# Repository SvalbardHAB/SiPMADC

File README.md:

# Existing SiPM ADC board

This board contains two dual-channel 10 bit 65MSPS MAX1182 ADCs; kindly provided by Maxim as free samples. There is also a MachXO2
CPLD for data processing, interfacing over SPI with a microcontroller. It is designed to obtain more  quantitative 
data from the SiPM and scintillator detector than the previous comparator board; at the expense of only using four of the 16 channels.

The board also contains the SiPM bias supply, consisting of a -34V inverting buck-boost converter and an op-amp to output the exact
voltage. This, along with the midpoint voltage - note this is not how the board is designed; during assembly a wire connecting 
Vmid to one of the DAC channels was added and U1 was not populated - is set by a TI DAC7564 allowing precise closed-case software adjustment.

At present the board has been assembled and tested. Unfortunately one of the ADC channels is not functioning correctly and
needs to be investigated further; this is suspected to be an assembly issue.

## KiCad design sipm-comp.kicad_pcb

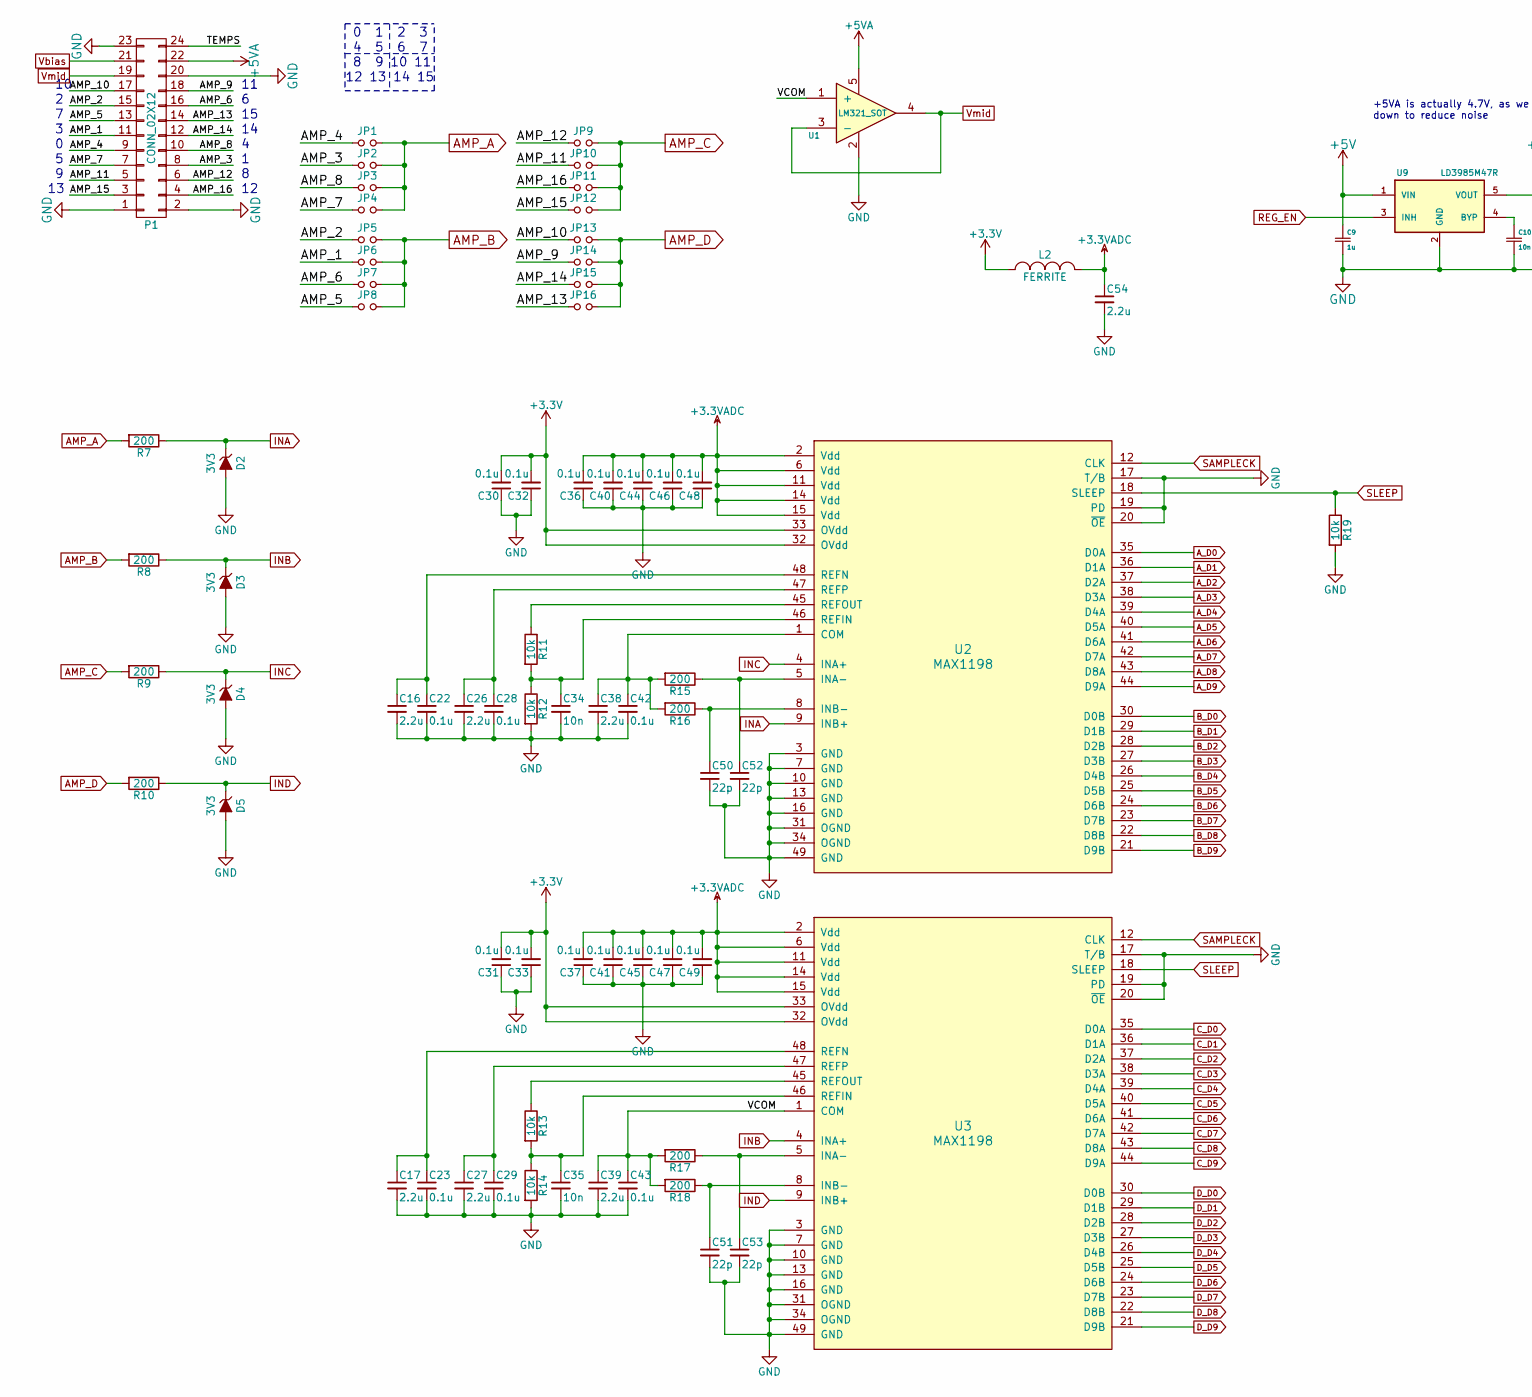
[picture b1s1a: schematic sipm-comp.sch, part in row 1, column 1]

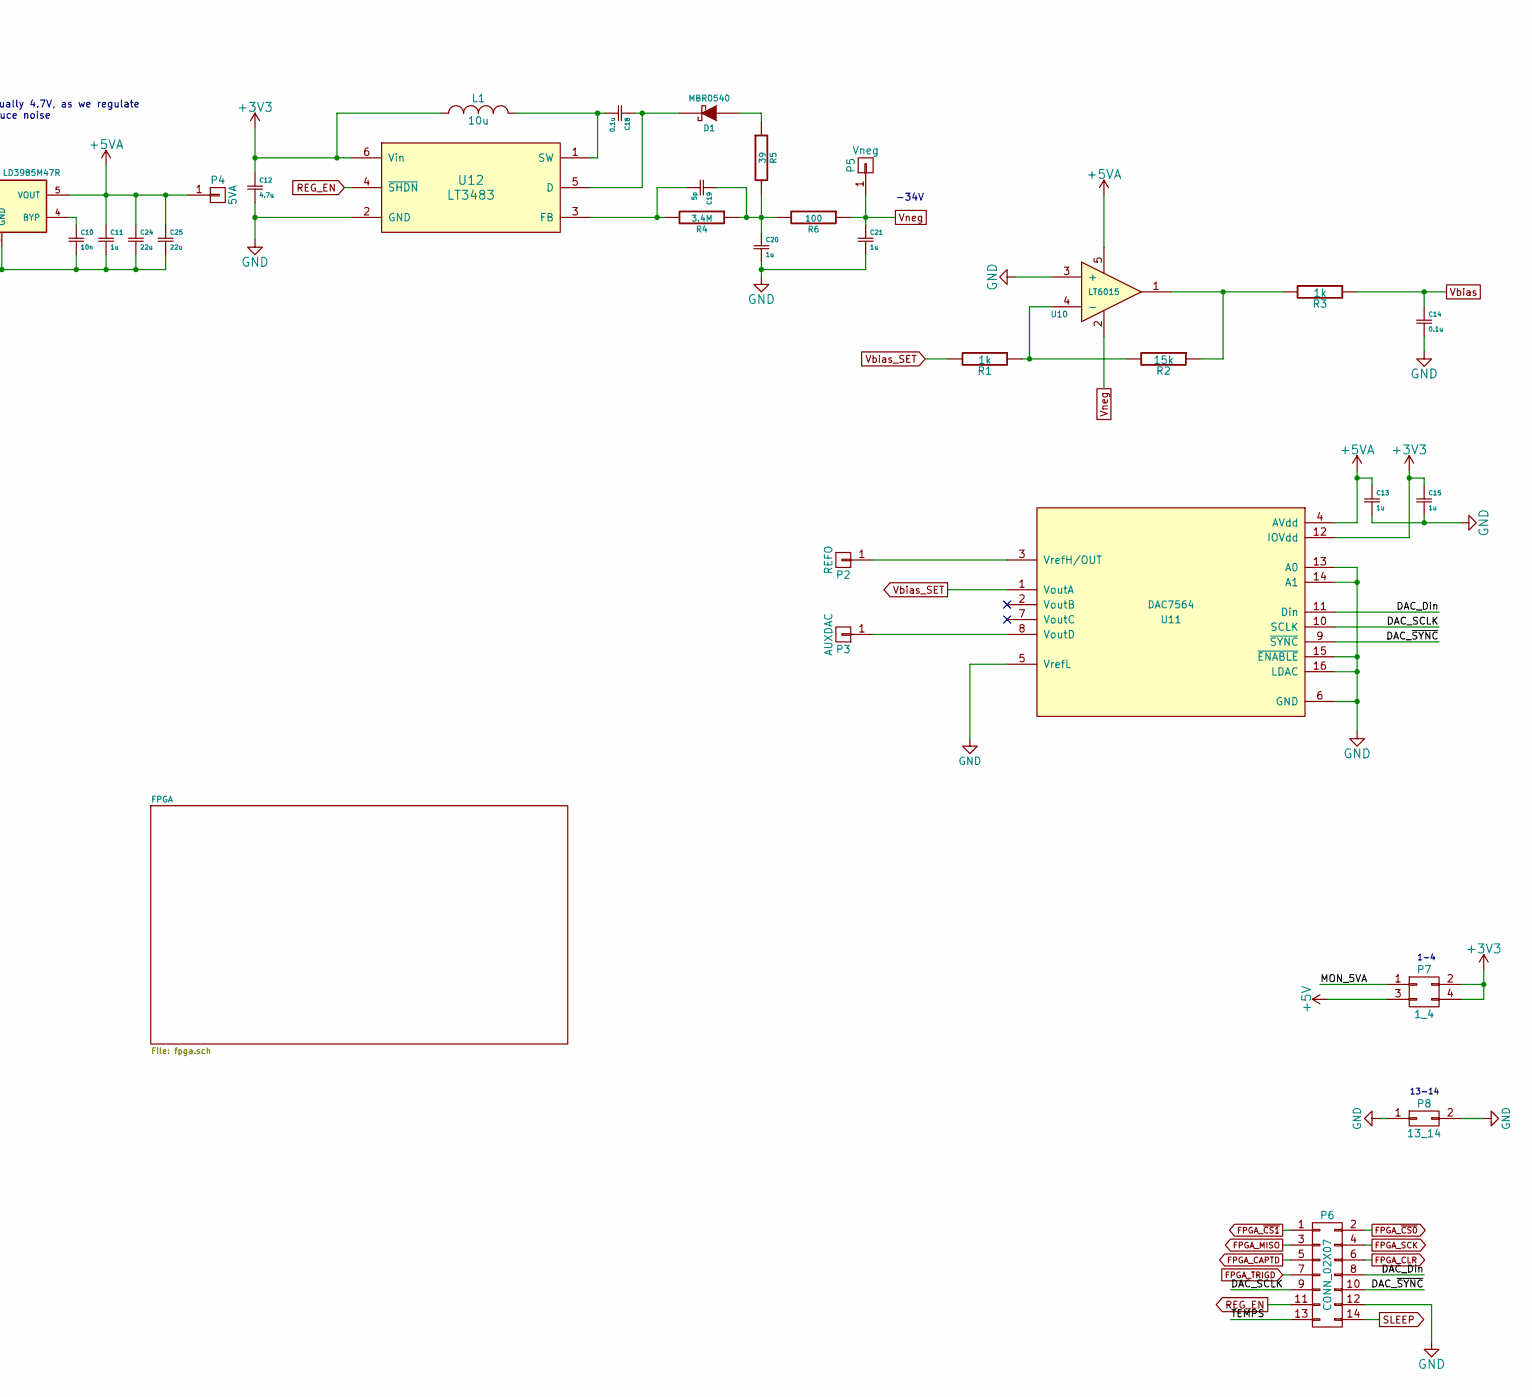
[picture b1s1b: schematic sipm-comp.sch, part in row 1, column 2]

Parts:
C9, C11, C13, C15: 1u; C_0603
C10, C34, C35: 10n; C_0402
C12: 4.7u; C_0805
C14, C18: 0.1u; C_0805
C16, C17, C26, C27, C38, C39, C54: 2.2u; C_0603
C19: 5p; C_0402
C20, C21: 1u; C_1206
C22, C23: 0.1u; C_0603
C24, C25: 22u; C_1206
C28, C29, C30, C31, C32, C33, C36, C37, C40, C41, C42, C43, C44, C45, C46, C47, C48, C49: 0.1u; C_0402
C50, C51, C52, C53: 22p; C_0402
D1: MBR0540; SOD-123
D2, D3, D4, D5: 3V3; SOD-123
JP1, JP2, JP3, JP4, JP5, JP6, JP7, JP8, JP9, JP10, JP11, JP12, JP13, JP14, JP15, JP16: Jumper_NO_Small; MINI_JMPR
L1: 10u; Neosid_Inductor_SM-NE45_SMD1812
L2: FERRITE; R_0805
P1: CONN_02X12; Pin_Header_Angled_2x12
P2: REFO; Measurement_Point_Round-SMD-Pad_Small
P3: AUXDAC; Measurement_Point_Round-SMD-Pad_Small
P4: 5VA; Measurement_Point_Round-SMD-Pad_Small
P5: Vneg; Measurement_Point_Round-SMD-Pad_Small
P6: CONN_02X07; Pin_Header_Straight_2x07
P7: 1_4; Pin_Header_Straight_2x02
P8: 13_14; Pin_Header_Straight_2x01
R1, R3: 1k; R_0402
R2: 15k; R_0402
R4: 3.4M; R_0402
R5: 39; R_0402
R6: 100; R_0402
R7, R8, R9, R10, R15, R16, R17, R18: 200; R_0402
R11, R12, R13, R14, R19: 10k; R_0402
U1: LM321_SOT; SOT-23-5
U2, U3: MAX1198; LQFP-48_7x7mm_EP4x4
U9: LD3985M47R; SOT-23-5
U10: LT6015; SOT-23-5
U11: DAC7564; TSSOP-16_4.4x5mm_Pitch0.65mm
U12: LT3483; SOT-23-6

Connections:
+3.3VADC: C36.2, C37.2, C40.2, C41.2, C44.2, C45.2, C46.2, C47.2, C48.2, C49.2, C54.1, L2.2, U2.2 (Vdd), U2.6 (Vdd), U2.11 (Vdd), U2.14 (Vdd), U2.15 (Vdd), U3.2 (Vdd), U3.6 (Vdd), U3.11 (Vdd), U3.14 (Vdd), U3.15 (Vdd)
+5V: C9.1, P7.3, U9.1 (VIN)
+5VA: C11.1, C13.1, C24.1, C25.1, P1.22, P4.1, U1.5, U9.5 (VOUT), U10.5, U11.4 (AVdd)
/AMP_1: JP6.1, P1.11
/AMP_2: JP5.1, P1.15
/AMP_3: JP2.1, P1.8
/AMP_4: JP1.1, P1.9
/AMP_5: JP8.1, P1.13
/AMP_6: JP7.1, P1.16
/AMP_7: JP4.1, P1.7
/AMP_8: JP3.1, P1.10
/AMP_9: JP14.1, P1.18
/AMP_10: JP13.1, P1.17
/AMP_11: JP10.1, P1.5
/AMP_12: JP9.1, P1.6
/AMP_13: JP16.1, P1.14
/AMP_14: JP15.1, P1.12
/AMP_15: JP12.1, P1.3
/AMP_16: JP11.1, P1.4
/DAC_Din: P6.8, U11.11 (Din)
/DAC_SCLK: P6.9, U11.10 (SCLK)
/DAC_~SYNC: P6.10, U11.9 (~SYNC)
/MON_5VA: P7.1
/TEMPS: P1.24, P6.13
/VCOM: C39.1, C43.1, R17.2, R18.2, U1.1 (+), U3.1 (COM)
AMP_A: JP1.2, JP2.2, JP3.2, JP4.2, R7.2
AMP_B: JP5.2, JP6.2, JP7.2, JP8.2, R8.2
AMP_C: JP9.2, JP10.2, JP11.2, JP12.2, R9.2
AMP_D: JP13.2, JP14.2, JP15.2, JP16.2, R10.2
A_D0: U2.35 (D0A); also elsewhere on the board
A_D1: U2.36 (D1A); also elsewhere on the board
A_D2: U2.37 (D2A); also elsewhere on the board
A_D3: U2.38 (D3A); also elsewhere on the board
A_D4: U2.39 (D4A); also elsewhere on the board
A_D5: U2.40 (D5A); also elsewhere on the board
A_D6: U2.41 (D6A); also elsewhere on the board
A_D7: U2.42 (D7A); also elsewhere on the board
A_D8: U2.43 (D8A); also elsewhere on the board
A_D9: U2.44 (D9A); also elsewhere on the board
B_D0: U2.30 (D0B); also elsewhere on the board
B_D1: U2.29 (D1B); also elsewhere on the board
B_D2: U2.28 (D2B); also elsewhere on the board
B_D3: U2.27 (D3B); also elsewhere on the board
B_D4: U2.26 (D4B); also elsewhere on the board
B_D5: U2.25 (D5B); also elsewhere on the board
B_D6: U2.24 (D6B); also elsewhere on the board
B_D7: U2.23 (D7B); also elsewhere on the board
B_D8: U2.22 (D8B); also elsewhere on the board
B_D9: U2.21 (D9B); also elsewhere on the board
C_D0: U3.35 (D0A); also elsewhere on the board
C_D1: U3.36 (D1A); also elsewhere on the board
C_D2: U3.37 (D2A); also elsewhere on the board
C_D3: U3.38 (D3A); also elsewhere on the board
C_D4: U3.39 (D4A); also elsewhere on the board
C_D5: U3.40 (D5A); also elsewhere on the board
C_D6: U3.41 (D6A); also elsewhere on the board
C_D7: U3.42 (D7A); also elsewhere on the board
C_D8: U3.43 (D8A); also elsewhere on the board
C_D9: U3.44 (D9A); also elsewhere on the board
D_D0: U3.30 (D0B); also elsewhere on the board
D_D1: U3.29 (D1B); also elsewhere on the board
D_D2: U3.28 (D2B); also elsewhere on the board
D_D3: U3.27 (D3B); also elsewhere on the board
D_D4: U3.26 (D4B); also elsewhere on the board
D_D5: U3.25 (D5B); also elsewhere on the board
D_D6: U3.24 (D6B); also elsewhere on the board
D_D7: U3.23 (D7B); also elsewhere on the board
D_D8: U3.22 (D8B); also elsewhere on the board
D_D9: U3.21 (D9B); also elsewhere on the board
FPGA_CAPTD: P6.5; also elsewhere on the board
FPGA_CLR: P6.6; also elsewhere on the board
FPGA_MISO: P6.3; also elsewhere on the board
FPGA_SCK: P6.4; also elsewhere on the board
FPGA_TRIGD: P6.7; also elsewhere on the board
FPGA_~CS0: P6.2; also elsewhere on the board
FPGA_~CS1: P6.1; also elsewhere on the board
GND: C9.2, C10.2, C11.2, C12.2, C13.2, C14.2, C15.2, C16.2, C17.2, C20.2, C21.2, C22.2, C23.2, C24.2, C25.2, C26.2, C27.2, C28.2, C29.2, C30.1, C31.1, C32.1, C33.1, C34.2, C35.2, C36.1, C37.1, C38.2, C39.2, C40.1, C41.1, C42.2, C43.2, C44.1, C45.1, C46.1, C47.1, C48.1, C49.1, C50.2, C51.2, C52.2, C53.2, C54.2, D2.2 (A), D3.2 (A), D4.2 (A), D5.2 (A), P1.1, P1.2, P1.20, P1.23, P6.12, P8.1, P8.2, R12.2, R14.2, R19.2, U1.2, U2.3 (GND), U2.7 (GND), U2.10 (GND), U2.13 (GND), U2.16 (GND), U2.17 (T/B), U2.19 (PD), U2.20 (~OE), U2.31 (OGND), U2.34 (OGND), U2.49 (GND), U3.3 (GND), U3.7 (GND), U3.10 (GND), U3.13 (GND), U3.16 (GND), U3.17 (T/B), U3.19 (PD), U3.20 (~OE), U3.31 (OGND), U3.34 (OGND), U3.49 (GND), U9.2 (GND), U10.3 (+), U11.5 (VrefL), U11.6 (GND), U11.13 (A0), U11.14 (A1), U11.15 (~ENABLE), U11.16 (LDAC), U12.2 (GND); also elsewhere on the board
INA: D2.1 (K), R7.1, U2.9 (INB+)
INB: D3.1 (K), R8.1, U3.4 (INA+)
INC: D4.1 (K), R9.1, U2.4 (INA+)
IND: D5.1 (K), R10.1, U3.9 (INB+)
unnamed: C10.1, U9.4 (BYP)
unnamed: C16.1, C22.1, U2.48 (REFN)
unnamed: C17.1, C23.1, U3.48 (REFN)
unnamed: C18.1, D1.2 (K), U12.5 (D)
unnamed: C18.2, L1.2, U12.1 (SW)
unnamed: C19.1, C20.1, R4.1, R5.2, R6.2
unnamed: C19.2, R4.2, U12.3 (FB)
unnamed: C26.1, C28.1, U2.47 (REFP)
unnamed: C27.1, C29.1, U3.47 (REFP)
unnamed: C34.1, R11.2, R12.1, U2.46 (REFIN)
unnamed: C35.1, R13.2, R14.1, U3.46 (REFIN)
unnamed: C38.1, C42.1, R15.2, R16.2, U2.1 (COM)
unnamed: C50.1, R16.1, U2.8 (INB-)
unnamed: C51.1, R18.1, U3.8 (INB-)
unnamed: C52.1, R15.1, U2.5 (INA-)
unnamed: C53.1, R17.1, U3.5 (INA-)
unnamed: D1.1 (A), R5.1
unnamed: P2.1, U11.3 (VrefH/OUT)
unnamed: P3.1, U11.8 (VoutD)
unnamed: R1.1, R2.2, U10.4 (-)
unnamed: R2.1, R3.2, U10.1
unnamed: R11.1, U2.45 (REFOUT)
unnamed: R13.1, U3.45 (REFOUT)
REG_EN: P6.11, U9.3 (INH), U12.4 (~SHDN)
SAMPLECK: U2.12 (CLK), U3.12 (CLK); also elsewhere on the board
SLEEP: P6.14, R19.1, U2.18 (SLEEP), U3.18 (SLEEP)
Vbias: C14.1, P1.21, R3.1
Vbias_SET: R1.2, U11.1 (VoutA)
Vmid: P1.19, U1.3 (-), U1.4
Vneg: C21.1, P5.1, R6.1, U10.2

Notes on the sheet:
+5VA is actually 4.7V, as we regulate down to reduce noise
-34V
1-4
13-14
0 1 2 3
4 5 6 7
8 9 10 11
12 13 14 15

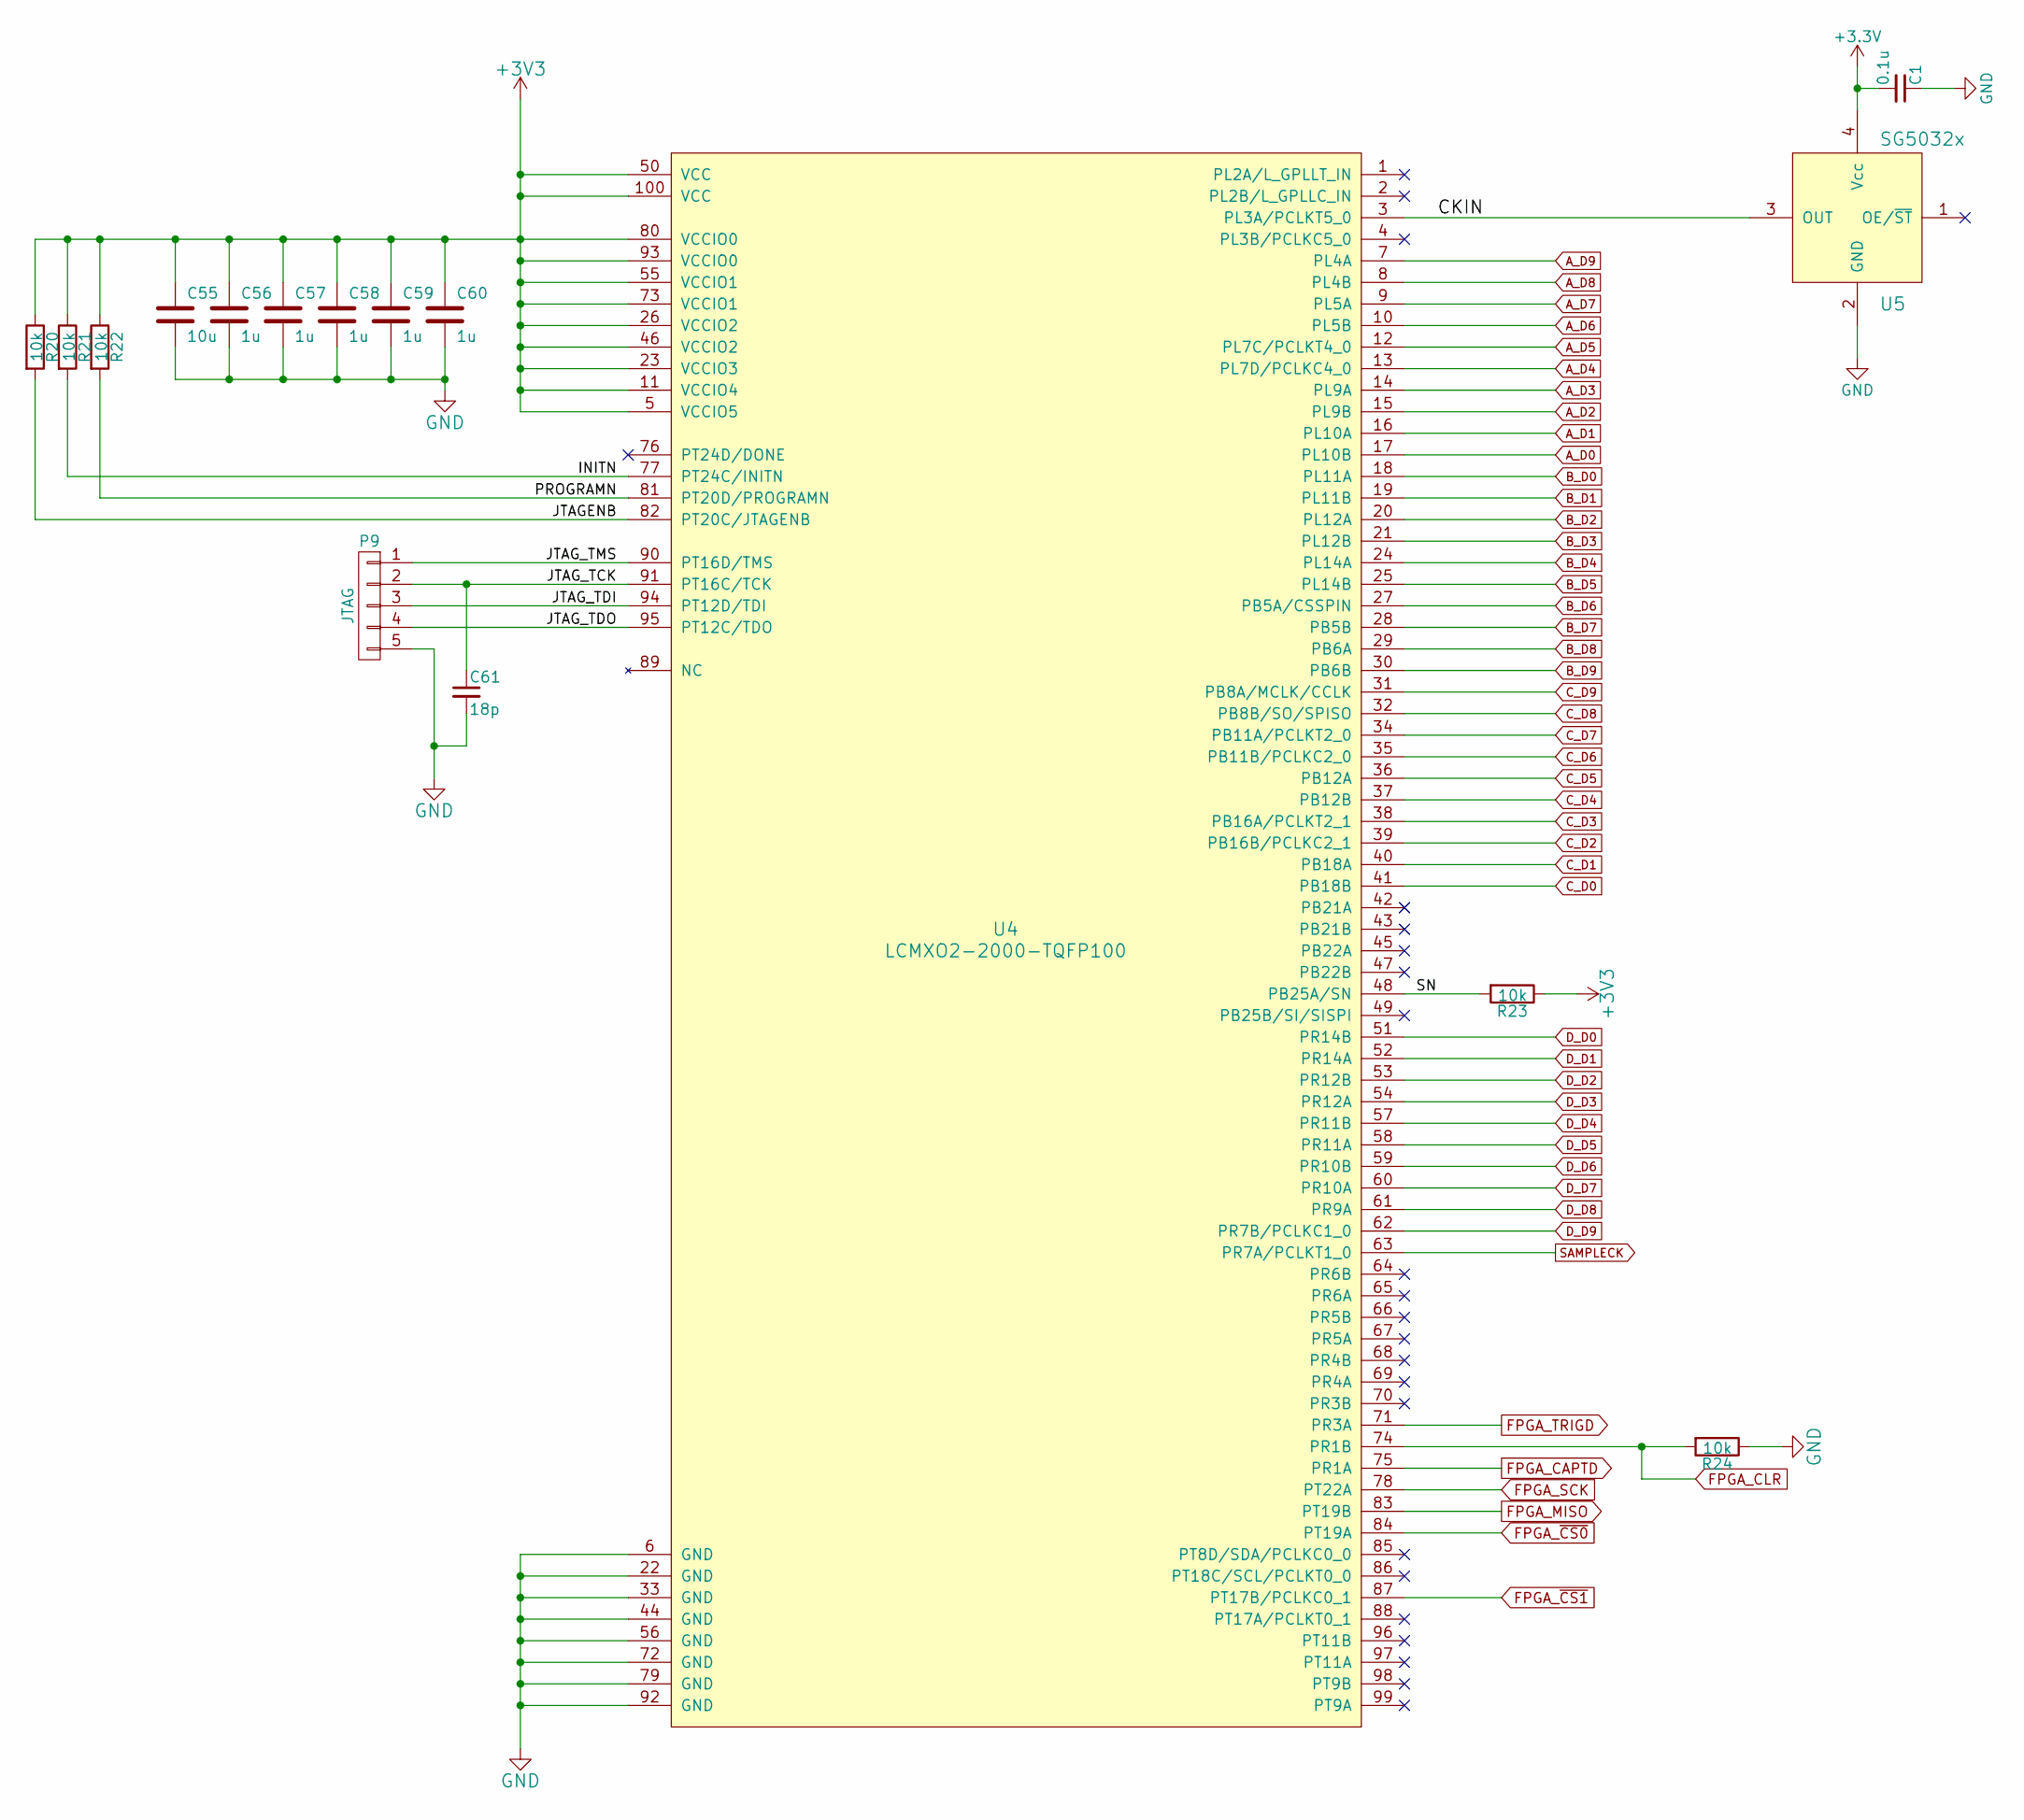
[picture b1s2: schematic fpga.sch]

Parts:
C1: 0.1u; C_0402
C55: 10u; C_0805
C56, C57, C58, C59, C60: 1u; C_0603
C61: 18p; C_0402
P9: JTAG; Pin_Header_Straight_1x05
R20, R21, R22, R23, R24: 10k; R_0402
U4: LCMXO2-2000-TQFP100; TQFP-100_14x14mm_Pitch0.5mm
U5: SG5032x; SG5032

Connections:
/FPGA/CKIN: U4.3 (PL3A/PCLKT5_0), U5.3 (OUT)
/FPGA/INITN: R21.2, U4.77 (PT24C/INITN)
/FPGA/JTAGENB: R20.2, U4.82 (PT20C/JTAGENB)
/FPGA/JTAG_TCK: C61.1, P9.2, U4.91 (PT16C/TCK)
/FPGA/JTAG_TDI: P9.3, U4.94 (PT12D/TDI)
/FPGA/JTAG_TDO: P9.4, U4.95 (PT12C/TDO)
/FPGA/JTAG_TMS: P9.1, U4.90 (PT16D/TMS)
/FPGA/PROGRAMN: R22.2, U4.81 (PT20D/PROGRAMN)
/FPGA/SN: R23.2, U4.48 (PB25A/SN)
A_D0: U4.17 (PL10B); also elsewhere on the board
A_D1: U4.16 (PL10A); also elsewhere on the board
A_D2: U4.15 (PL9B); also elsewhere on the board
A_D3: U4.14 (PL9A); also elsewhere on the board
A_D4: U4.13 (PL7D/PCLKC4_0); also elsewhere on the board
A_D5: U4.12 (PL7C/PCLKT4_0); also elsewhere on the board
A_D6: U4.10 (PL5B); also elsewhere on the board
A_D7: U4.9 (PL5A); also elsewhere on the board
A_D8: U4.8 (PL4B); also elsewhere on the board
A_D9: U4.7 (PL4A); also elsewhere on the board
B_D0: U4.18 (PL11A); also elsewhere on the board
B_D1: U4.19 (PL11B); also elsewhere on the board
B_D2: U4.20 (PL12A); also elsewhere on the board
B_D3: U4.21 (PL12B); also elsewhere on the board
B_D4: U4.24 (PL14A); also elsewhere on the board
B_D5: U4.25 (PL14B); also elsewhere on the board
B_D6: U4.27 (PB5A/CSSPIN); also elsewhere on the board
B_D7: U4.28 (PB5B); also elsewhere on the board
B_D8: U4.29 (PB6A); also elsewhere on the board
B_D9: U4.30 (PB6B); also elsewhere on the board
C_D0: U4.41 (PB18B); also elsewhere on the board
C_D1: U4.40 (PB18A); also elsewhere on the board
C_D2: U4.39 (PB16B/PCLKC2_1); also elsewhere on the board
C_D3: U4.38 (PB16A/PCLKT2_1); also elsewhere on the board
C_D4: U4.37 (PB12B); also elsewhere on the board
C_D5: U4.36 (PB12A); also elsewhere on the board
C_D6: U4.35 (PB11B/PCLKC2_0); also elsewhere on the board
C_D7: U4.34 (PB11A/PCLKT2_0); also elsewhere on the board
C_D8: U4.32 (PB8B/SO/SPISO); also elsewhere on the board
C_D9: U4.31 (PB8A/MCLK/CCLK); also elsewhere on the board
D_D0: U4.51 (PR14B); also elsewhere on the board
D_D1: U4.52 (PR14A); also elsewhere on the board
D_D2: U4.53 (PR12B); also elsewhere on the board
D_D3: U4.54 (PR12A); also elsewhere on the board
D_D4: U4.57 (PR11B); also elsewhere on the board
D_D5: U4.58 (PR11A); also elsewhere on the board
D_D6: U4.59 (PR10B); also elsewhere on the board
D_D7: U4.60 (PR10A); also elsewhere on the board
D_D8: U4.61 (PR9A); also elsewhere on the board
D_D9: U4.62 (PR7B/PCLKC1_0); also elsewhere on the board
FPGA_CAPTD: U4.75 (PR1A); also elsewhere on the board
FPGA_CLR: R24.2, U4.74 (PR1B); also elsewhere on the board
FPGA_MISO: U4.83 (PT19B); also elsewhere on the board
FPGA_SCK: U4.78 (PT22A); also elsewhere on the board
FPGA_TRIGD: U4.71 (PR3A); also elsewhere on the board
FPGA_~CS0: U4.84 (PT19A); also elsewhere on the board
FPGA_~CS1: U4.87 (PT17B/PCLKC0_1); also elsewhere on the board
GND: C1.1, C55.2, C56.2, C57.2, C58.2, C59.2, C60.2, C61.2, P9.5, R24.1, U4.6 (GND), U4.22 (GND), U4.33 (GND), U4.44 (GND), U4.56 (GND), U4.72 (GND), U4.79 (GND), U4.92 (GND), U5.2 (GND); also elsewhere on the board
SAMPLECK: U4.63 (PR7A/PCLKT1_0); also elsewhere on the board

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
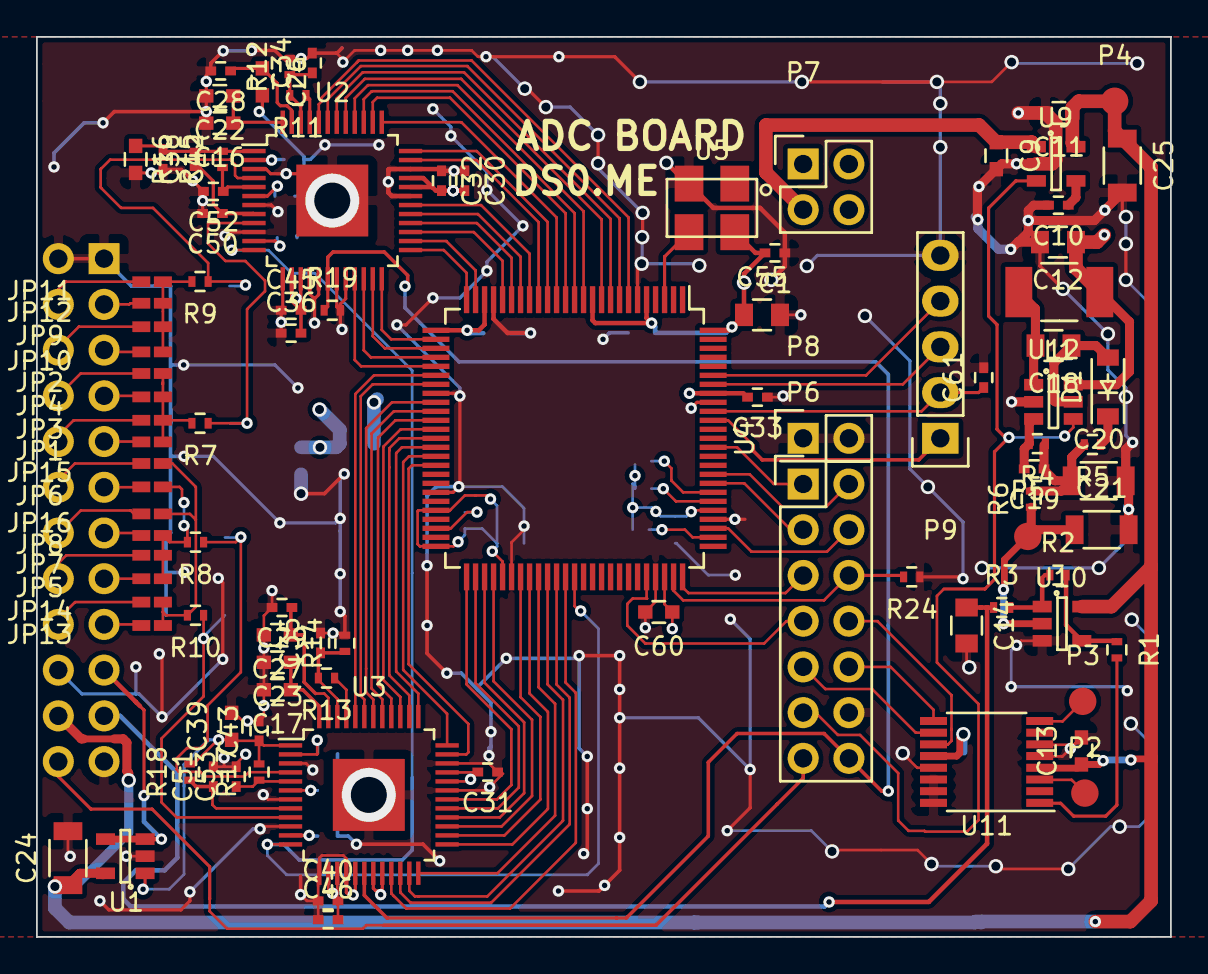
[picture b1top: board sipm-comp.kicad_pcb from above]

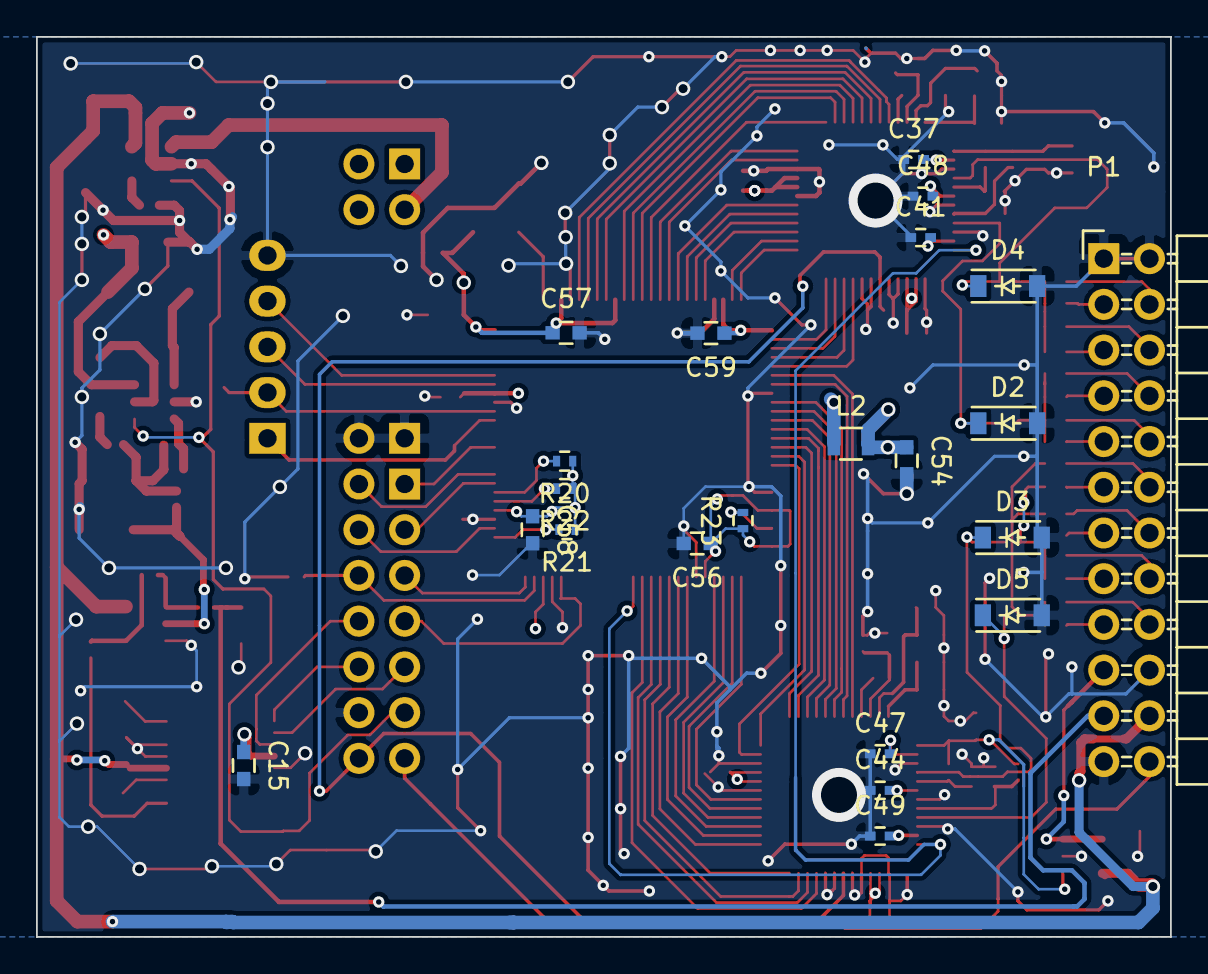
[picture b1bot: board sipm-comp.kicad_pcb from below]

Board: 4 copper layers, 63.0 x 50.0 mm, 119 parts (22 on the bottom side), 120 nets.

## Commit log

2016-07-07 Add existing design files for ADC board
